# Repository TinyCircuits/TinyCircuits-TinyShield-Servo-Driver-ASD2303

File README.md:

# TinyCircuits-TinyShield-Servo-Driver-ASD2303
# ASD2303 Rev3

These are the design files for the TinyCircuits ASD2021 Rev 3 PCB.  This is a TinyShield (Square Version, 20mm x 20mm) that can drive up to four servos at a time.  

Format is in Cadsoft Eagle format - Eagle version 6.2 was used for the original design.

For more infomation on this, check out the product page at TinyCircuits.com:  https://tinycircuits.com/collections/motors/products/servo-tinyshield

# License:

Design by TinyCircuits.
All design files are released under the Creative Commons Attribution Share-Alike 3.0 License, see the following link for details: http://creativecommons.org/licenses/by-sa/3.0

All text above must be included in any redistribution or derived design

This project uses designs and concepts developed as part of the Arduino project and the LilyPad project.  The TinyCircuits design files themselves (schematics, PCB and libraries) are not directly derived from these works' design files and have been created new, however the concepts and basic architecture behind the TinyDuino and TinyLily products are derived and we thank the hard work of the organizations below for their contributions to open-source hardware:
  
Original Arduino Uno Design by Team Arduino

LilyPad Arduino Design by Leah Buechley and Sparkfun Electronics

Please support the open-source hardware community

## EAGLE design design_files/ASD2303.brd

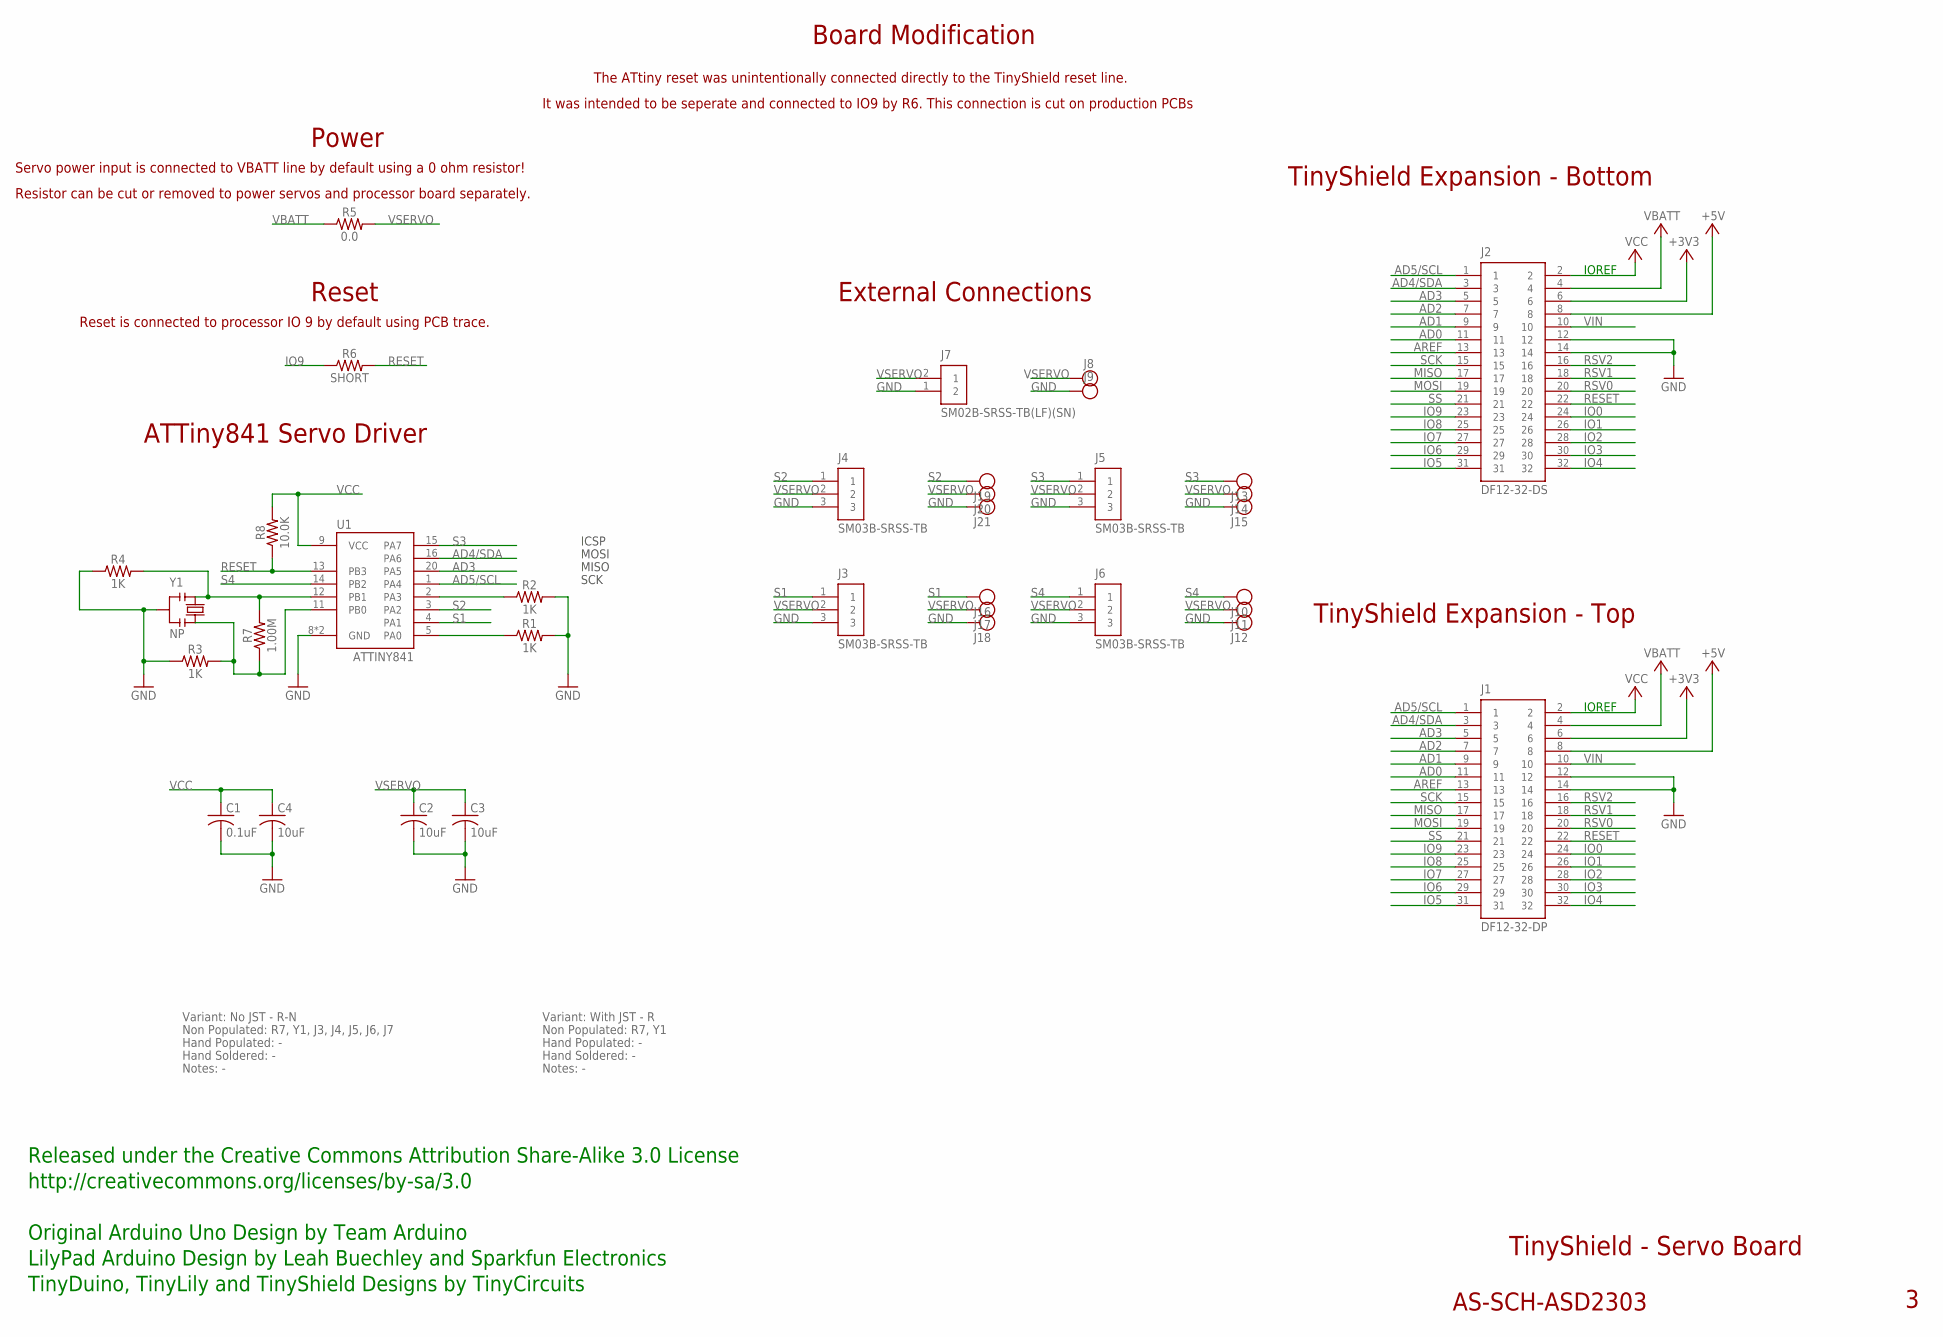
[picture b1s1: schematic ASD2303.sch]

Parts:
C1: 0.1uF; C0402
C2, C3, C4: 10uF; C0805
J1: DF12-32-DP; PARTNO AS-ITM-00015
J2: DF12-32-DS; PARTNO AS-ITM-00012
J3, J4, J5, J6: SM03B-SRSS-TB; JST_SH_3X1
J7: SM02B-SRSS-TB(LF)(SN); JST_SH_2X1
J8, J9, J10, J11, J12, J13, J14, J15, J16, J17, J18, J19, J20, J21: PIN_1X.1"1; 1X.1"_2
R1, R2, R3, R4: 1K; 0402; PARTNO AS-ITM-00003
R5: 0.0; 0402
R6: SHORT; 0402_SHORT
R7: 1.00M; 0402
R8: 10.0K; 0402
U1: ATTINY841; VQFN-20
Y1: NP; RESONATOR_SMALL; PARTNO AS-ITM-00027

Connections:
+3V3: J1.6, J2.6
+5V: J1.8, J2.8
AD0: J1.11, J2.11
AD1: J1.9, J2.9
AD2: J1.7, J2.7
AD3: J1.5, J2.5, U1.20 (PA5)
AD4/SDA: J1.3, J2.3, U1.16 (PA6)
AD5/SCL: J1.1, J2.1, U1.1 (PA4)
AREF: J1.13, J2.13
GND: C1.2, C2.2, C3.2, C4.2, J1.12, J1.14, J2.12, J2.14, J3.3, J4.3, J5.3, J6.3, J7.1 (2), J9.1, J12.1, J15.1, J18.1, J21.1, R1.2, R2.2, R3.1, R4.1, U1.8 (GND), U1.PAD (GND), Y1.2
IO0: J1.24, J2.24
IO1: J1.26, J2.26
IO2: J1.28, J2.28
IO3: J1.30, J2.30
IO4: J1.32, J2.32
IO5: J1.31, J2.31
IO6: J1.29, J2.29
IO7: J1.27, J2.27
IO8: J1.25, J2.25
IO9: J1.23, J2.23, R6.1
MISO: J1.17, J2.17
MOSI: J1.19, J2.19
unnamed: R4.2, R7.2, U1.12 (PB1), Y1.1
unnamed: R3.2, R7.1, U1.11 (PB0), Y1.3
unnamed: R2.1, U1.2 (PA3)
unnamed: R1.1, U1.5 (PA0)
RESET: J1.22, J2.22, R6.2, R8.1, U1.13 (PB3)
RSV0: J1.20, J2.20
RSV1: J1.18, J2.18
RSV2: J1.16, J2.16
S1: J3.1, J16.1, U1.4 (PA1)
S2: J4.1, J19.1, U1.3 (PA2)
S3: J5.1, J13.1, U1.15 (PA7)
S4: J6.1, J10.1, U1.14 (PB2)
SCK: J1.15, J2.15
SS: J1.21, J2.21
VBATT: J1.4, J2.4, R5.1
VCC: C1.1, C4.1, J1.2, J2.2, R8.2, U1.9 (VCC)
VIN: J1.10, J2.10
VSERVO: C2.1, C3.1, J3.2, J4.2, J5.2, J6.2, J7.2 (1), J8.1, J11.1, J14.1, J17.1, J20.1, R5.2

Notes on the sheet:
TinyShield Expansion - Bottom
TinyShield - Servo Board
AS-SCH-ASD2303
TinyShield Expansion - Top
IOREF
Released under the Creative Commons Attribution Share-Alike 3.0 License
http://creativecommons.org/licenses/by-sa/3.0
LilyPad Arduino Design by Leah Buechley and Sparkfun Electronics
TinyDuino, TinyLily and TinyShield Designs by TinyCircuits
Original Arduino Uno Design by Team Arduino
External Connections
ATTiny841 Servo Driver
MOSI
MISO
SCK
ICSP
Power
Resistor can be cut or removed to power servos and processor board separately.
Reset
Reset is connected to processor IO 9 by default using PCB trace.
Servo power input is connected to VBATT line by default using a 0 ohm resistor!
Board Modification
The ATtiny reset was unintentionally connected directly to the TinyShield reset line.
It was intended to be seperate and connected to IO9 by R6. This connection is cut on production PCBs
Variant: No JST - R-N
Non Populated: R7, Y1, J3, J4, J5, J6, J7
Hand Populated: -
Hand Soldered: -
Notes: -
Variant: With JST - R
Non Populated: R7, Y1

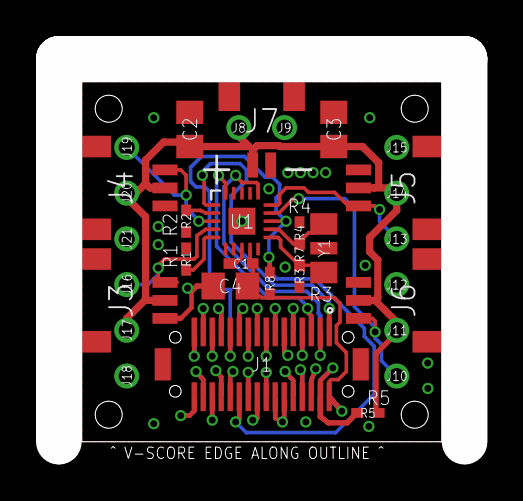
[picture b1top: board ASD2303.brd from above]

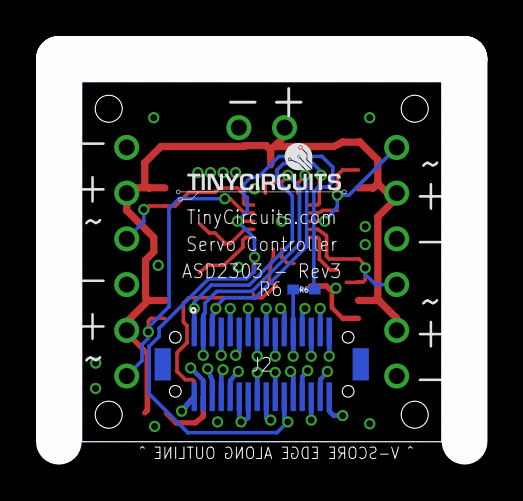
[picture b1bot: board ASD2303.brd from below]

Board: 2 copper layers, 20.0 x 20.0 mm, 36 parts (2 on the bottom side), 40 nets.

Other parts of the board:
U$1: DOCFIELD-TINYCIRCUITS-PCB

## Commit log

2019-01-04 Update format
2019-04-19 add pictures
2019-04-19 Add zip file
2019-04-19 add zip
2019-05-20 renamed files to standard
2019-05-20 updateed naming
2019-05-22 added images
2019-05-23 updated images
2020-02-11 image update
2020-07-28 Add CAD data
2020-08-14 Update CAD drawing
